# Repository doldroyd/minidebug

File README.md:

# minidebug

todo:
find a specific nfet
NLSX level translator (1.8-5v)
MX25R16 (verify footprint)
verify LVC125 1.8-5v, use soic-8 footprint?
find ferrite beads
make my own ferrite symbol
add resistors to signal lines?
do we really need the 32khz crystal?
make bom with links

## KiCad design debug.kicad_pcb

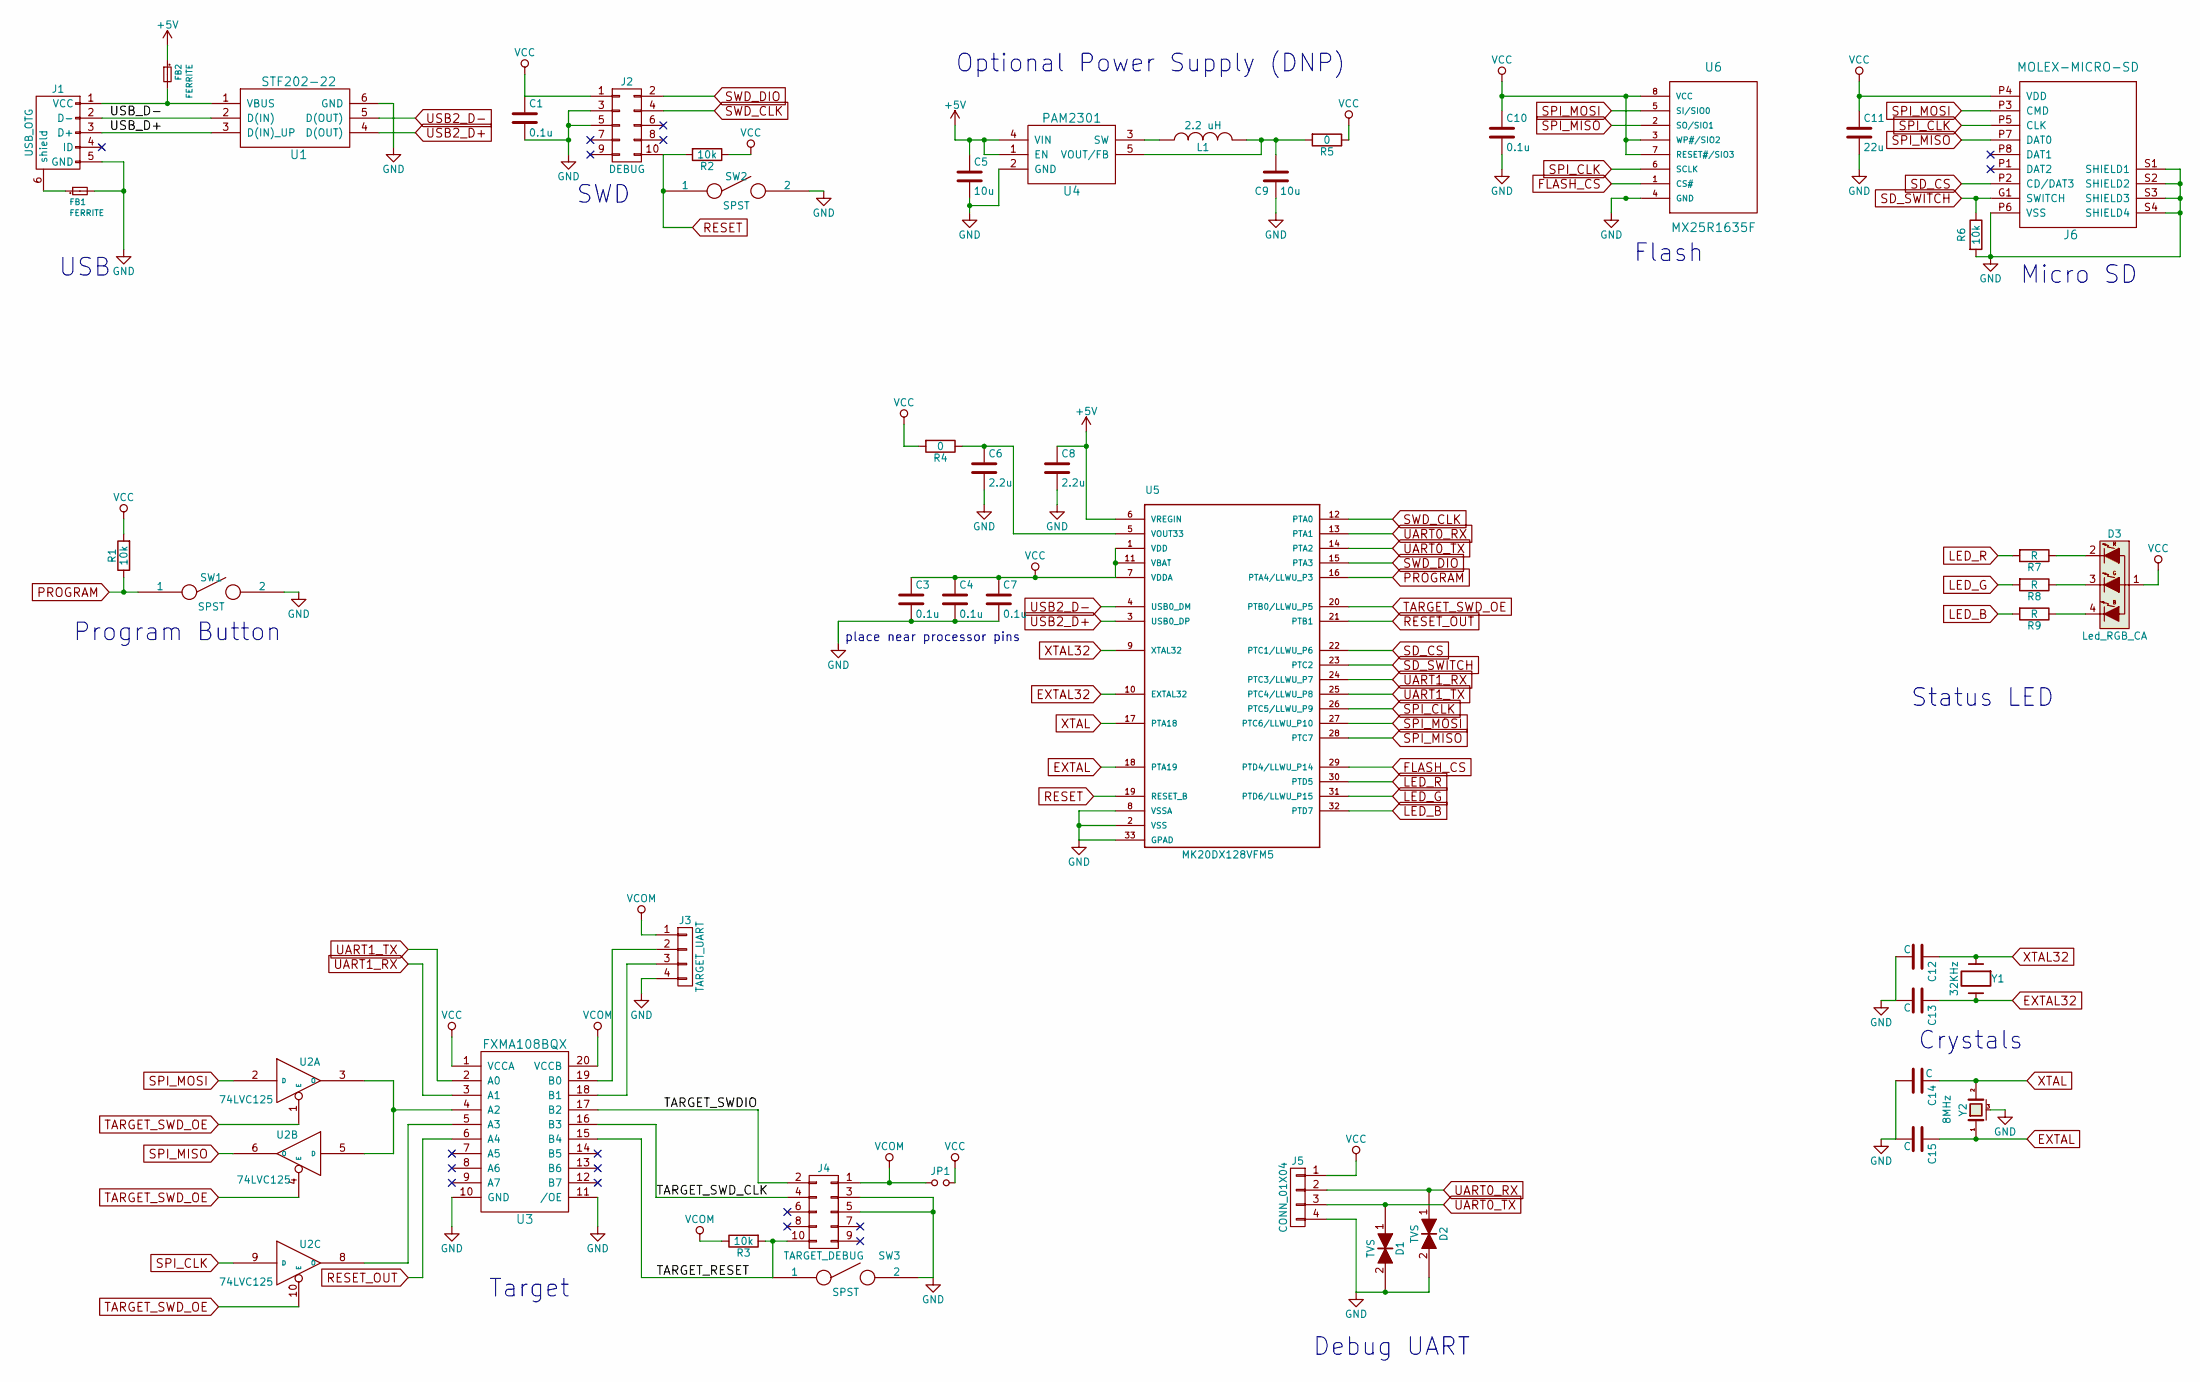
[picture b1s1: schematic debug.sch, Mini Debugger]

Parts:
C1, C3, C4, C7, C10: 0.1u; C_0603
C5, C9: 10u; C_0603
C6, C8: 2.2u; C_0603
C11: 22u; C_0603
C12, C13, C14, C15: C; C_0603
D1, D2: TVS; R_0603
D3: Led_RGB_CA; PLCC4
FB1, FB2: FERRITE; R_0603
J1: USB_OTG; USB_Mini-B
J2: DEBUG; Pin_Header_Straight_2x05_Pitch1.27mm
J3: TARGET_UART; Pin_Header_Straight_1x04
J4: TARGET_DEBUG; Pin_Header_Straight_2x05_Pitch1.27mm
J5: CONN_01X04; Pin_Header_Straight_1x04
J6: MOLEX-MICRO-SD; SD-105027-001
JP1: Jumper_NO_Small; Pin_Header_Straight_1x02
L1: 2.2 uH; 1008
R1, R2, R3, R6: 10k; R_0603
R4, R5: 0; R_0603
R7, R8, R9: R; R_0603
SW1, SW2, SW3: SPST; PTS645SM43SMTR92
U1: STF202-22; SOT457
U2: 74LVC125; DHVQFN14
U3: FXMA108BQX; DQFN20
U4: PAM2301; SOT-23-5
U5: MK20DX128VFM5
U6: MX25R1635F; SOIC-8-N
Y1: 32KHz; FX135
Y2: 8MHz; Crystal_SMD_5032_4Pads

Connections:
+5V: C5.1, C8.1, FB2.1, U4.1 (EN), U4.4 (VIN), U5.6 (VREGIN)
/TARGET_RESET: J4.10, R3.2, SW3.1, U3.15 (B4)
/TARGET_SWDIO: J4.2, U3.17 (B2)
/TARGET_SWD_CLK: J4.4, U3.16 (B3)
/USB_D+: J1.3 (D+), U1.3 (D(IN)_UP)
/USB_D-: J1.2 (D-), U1.2 (D(IN))
EXTAL: C15.1, U5.18 (PTA19), Y2.1
EXTAL32: C13.1, U5.10 (EXTAL32), Y1.2
FLASH_CS: U5.29 (PTD4/LLWU_P14), U6.1 (CS#)
GND: C1.2, C3.2, C4.2, C5.2, C6.2, C7.2, C8.2, C9.2, C10.2, C11.2, C12.2, C13.2, C14.2, C15.2, D1.2, D2.2, FB1.2, J1.5 (GND), J2.3, J2.5, J3.4, J4.3, J4.5, J5.4, J6.P6 (VSS), J6.S1 (SHIELD1), J6.S2 (SHIELD2), J6.S3 (SHIELD3), J6.S4 (SHIELD4), R6.2, SW1.2, SW2.2, SW3.2, U1.6 (GND), U2.7 (GND), U3.10 (GND), U3.11 (/OE), U4.2 (GND), U5.2 (VSS), U5.8 (VSSA), U5.33 (GPAD), U6.4 (GND), Y2.3 (case)
LED_B: R9.2, U5.32 (PTD7)
LED_G: R8.2, U5.31 (PTD6/LLWU_P15)
LED_R: R7.2, U5.30 (PTD5)
unnamed: C6.1, R4.1, U5.5 (VOUT33)
unnamed: C9.1, L1.2, R5.2, U4.5 (VOUT/FB)
unnamed: D3.2 (R), R7.1
unnamed: D3.3 (G), R8.1
unnamed: D3.4 (B), R9.1
unnamed: FB1.1, J1.6 (shield)
unnamed: FB2.2, J1.1 (VCC), U1.1 (VBUS)
unnamed: J3.2, U3.19 (B0)
unnamed: J3.3, U3.18 (B1)
unnamed: L1.1, U4.3 (SW)
unnamed: U2.3 (O), U2.5 (D), U3.4 (A2)
unnamed: U2.8 (O), U3.5 (A3)
PROGRAM: R1.1, SW1.1, U5.16 (PTA4/LLWU_P3)
RESET: J2.10, R2.2, SW2.1, U5.19 (RESET_B)
RESET_OUT: U3.6 (A4), U5.21 (PTB1)
SD_CS: J6.P2 (CD/DAT3), U5.22 (PTC1/LLWU_P6)
SD_SWITCH: J6.G1 (SWITCH), R6.1, U5.23 (PTC2)
SPI_CLK: J6.P5 (CLK), U2.9 (D), U5.26 (PTC5/LLWU_P9), U6.6 (SCLK)
SPI_MISO: J6.P7 (DAT0), U2.6 (O), U5.28 (PTC7), U6.2 (SO/SIO1)
SPI_MOSI: J6.P3 (CMD), U2.2 (D), U5.27 (PTC6/LLWU_P10), U6.5 (SI/SIO0)
SWD_CLK: J2.4, U5.12 (PTA0)
SWD_DIO: J2.2, U5.15 (PTA3)
TARGET_SWD_OE: U2.1 (E), U2.4 (E), U2.10 (E), U5.20 (PTB0/LLWU_P5)
UART0_RX: D2.1, J5.2, U5.13 (PTA1)
UART0_TX: D1.1, J5.3, U5.14 (PTA2)
UART1_RX: U3.3 (A1), U5.24 (PTC3/LLWU_P7)
UART1_TX: U3.2 (A0), U5.25 (PTC4/LLWU_P8)
USB2_D+: U1.4 (D(OUT)), U5.3 (USB0_DP)
USB2_D-: U1.5 (D(OUT)), U5.4 (USB0_DM)
VCC: C1.1, C3.1, C4.1, C7.1, C10.1, C11.1, D3.1, J2.1, J5.1, J6.P4 (VDD), JP1.2, R1.2, R2.1, R4.2, R5.1, U2.14 (VCC), U3.1 (VCCA), U5.1 (VDD), U5.7 (VDDA), U5.11 (VBAT), U6.3 (WP#/SIO2), U6.7 (RESET#/SIO3), U6.8 (VCC)
VCOM: J3.1, J4.1, JP1.1, R3.1, U3.20 (VCCB)
XTAL: C14.1, U5.17 (PTA18), Y2.2
XTAL32: C12.1, U5.9 (XTAL32), Y1.1

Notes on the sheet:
Target
Program Button
Debug UART
SWD
USB
Flash
Micro SD
Status LED
place near processor pins
Optional Power Supply (DNP)
Crystals

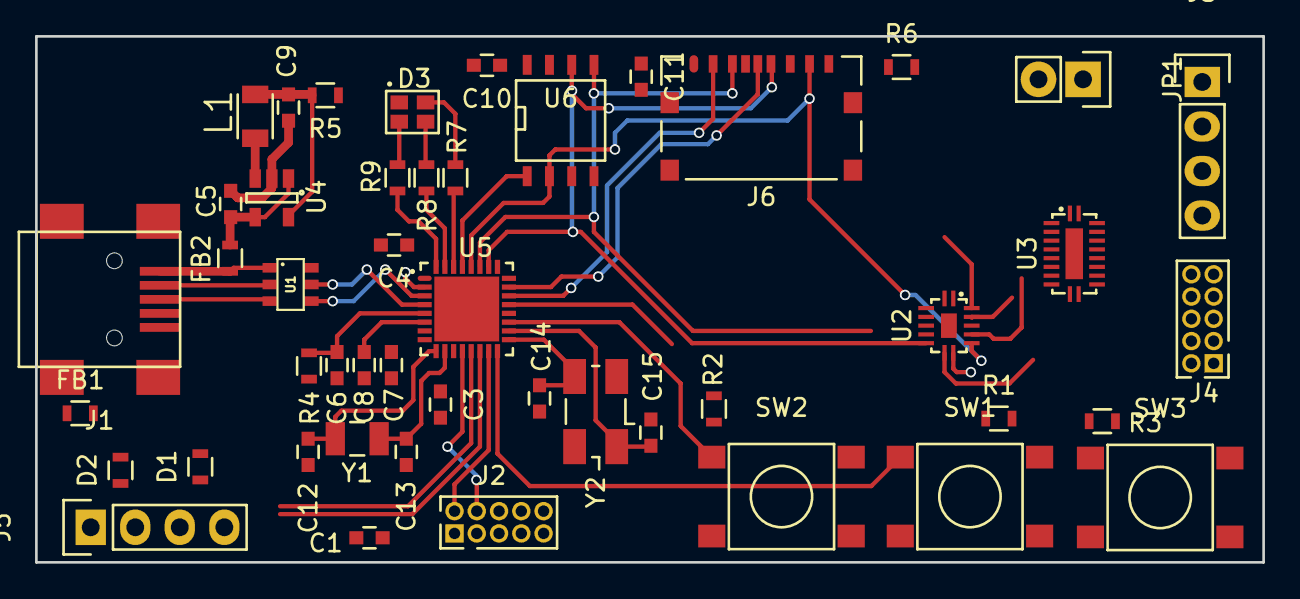
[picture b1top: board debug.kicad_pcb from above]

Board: 2 copper layers, 70.0 x 30.0 mm, 47 parts (0 on the bottom side), 46 nets.

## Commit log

2016-11-01 progress
2016-11-01 more progress
2016-11-05 update pdf
2016-11-07 minor sch tweaks, starting to route (poorly)
2016-11-15 replace large components with smaller ones
    change to simple switching power supply
    add board outline
    simplify USB protection
2016-11-16 progress
    simplify LEDs
    fix ferrite bead on 5v
    lots of routing I'll have to redo anyway later

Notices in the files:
parts and their libraries:
Copyright 2016 Accelerated Designs. All rights reserved.
